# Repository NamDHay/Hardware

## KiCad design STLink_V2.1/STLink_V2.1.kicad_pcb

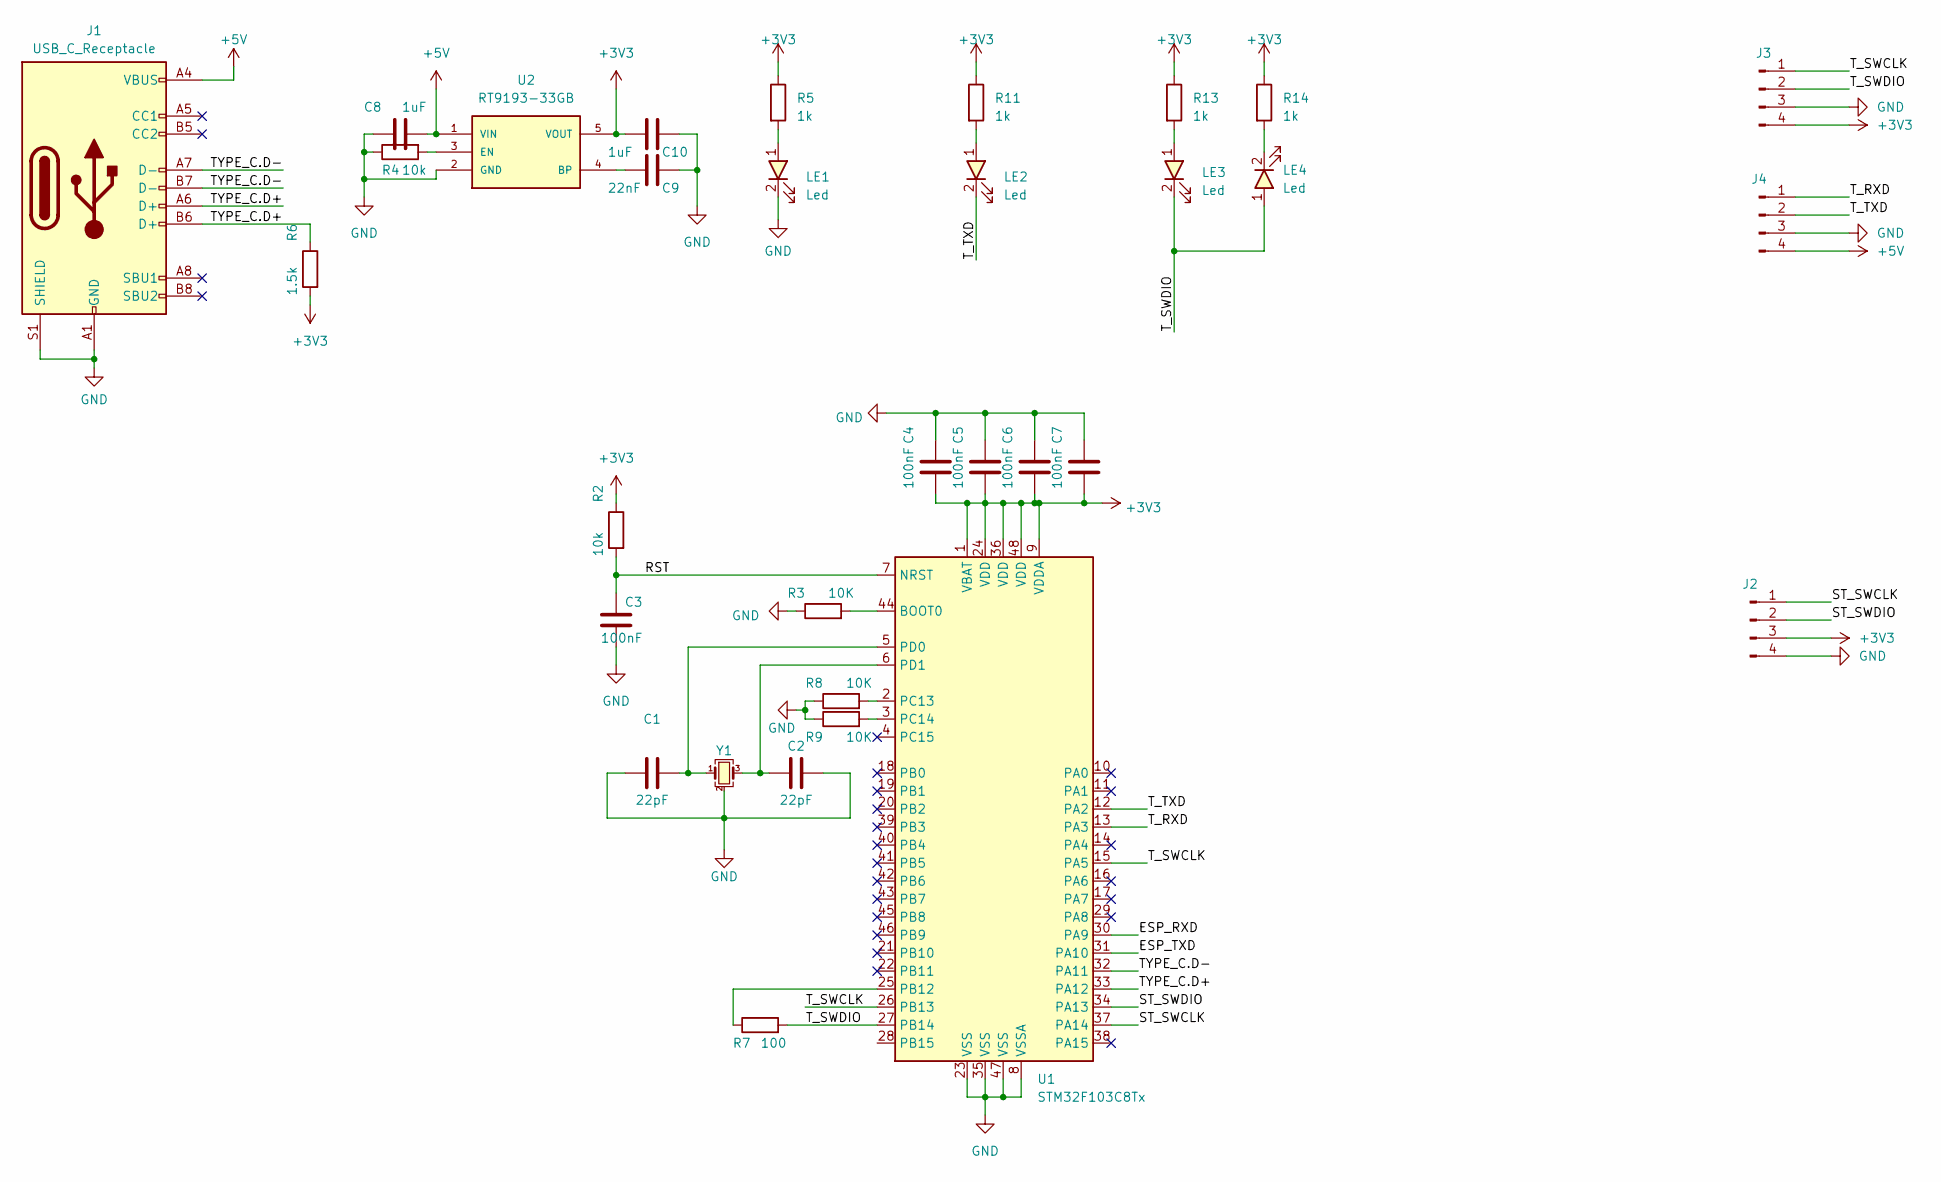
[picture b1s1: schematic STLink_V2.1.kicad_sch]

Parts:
C1, C2: 22pF; C_0603
C3, C4, C5, C6, C7: 100nF; C_0603
C8, C10: 1uF; C_0603
C9: 22nF; C_0603
J1: USB_C_Receptacle; USB_C_Receptacle_XKB_U262-16XN-4BVC11
J2, J3, J4: Conn_01x04_Pin; Conn-Horz-SMD-4P-2.54mm-PinHeader
LE1, LE2, LE3, LE4: Led; LED_0603
R2, R4: 10k; R_0603
R3, R8, R9: 10K; R_0603
R5, R11, R13, R14: 1k; R_0603
R6: 1.5k; R_0603
R7: 100; R_0603
U1: STM32F103C8Tx; LQFP-48_7x7mm_P0.5mm
U2: RT9193-33GB; SOT23-5
Y1: Crystal_GND24_Small; Crystal-SMD-4P-3.2x2.6mm-3225

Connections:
+3V3: C4.2, C5.2, C6.2, C7.2, C10.2, J2.3, J3.4, R2.1, R5.1, R6.2, R11.1, R13.1, R14.1, U1.1 (VBAT), U1.9 (VDDA), U1.24 (VDD), U1.36 (VDD), U1.48 (VDD), U2.5 (VOUT)
+5V: C8.2, J1.A4 (VBUS), J1.A9 (VBUS), J1.B4 (VBUS), J1.B9 (VBUS), J4.4, U2.1 (VIN)
/ESP_RXD: U1.30 (PA9)
/ESP_TXD: U1.31 (PA10)
/RST: C3.1, R2.2, U1.7 (NRST)
/ST_SWCLK: J2.1, U1.37 (PA14)
/ST_SWDIO: J2.2, U1.34 (PA13)
/TYPE_C.D+: J1.A6 (D+), J1.B6 (D+), R6.1, U1.33 (PA12)
/TYPE_C.D-: J1.A7 (D-), J1.B7 (D-), U1.32 (PA11)
/T_RXD: J4.1, U1.13 (PA3)
/T_SWCLK: J3.1, U1.15 (PA5), U1.26 (PB13)
/T_SWDIO: J3.2, LE3.2, LE4.1, R7.2, U1.27 (PB14)
/T_TXD: J4.2, LE2.2, U1.12 (PA2)
GND: C1.1, C2.2, C3.2, C4.1, C5.1, C6.1, C7.1, C8.1, C9.1, C10.1, J1.A1 (GND), J1.A12 (GND), J1.B1 (GND), J1.B12 (GND), J1.S1 (SHIELD), J2.4, J3.3, J4.3, LE1.2, R3.1, R4.1, R8.1, R9.1, U1.8 (VSSA), U1.23 (VSS), U1.35 (VSS), U1.47 (VSS), U2.2 (GND), Y1.2, Y1.4
unnamed: LE1.1, R5.2
unnamed: LE2.1, R11.2
unnamed: LE3.1, R13.2
unnamed: LE4.2, R14.2
unnamed: R3.2, U1.44 (BOOT0)
unnamed: R7.1, U1.25 (PB12)
unnamed: R8.2, U1.2 (PC13)
unnamed: R9.2, U1.3 (PC14)
unnamed: C1.2, U1.5 (PD0), Y1.1
unnamed: C2.1, U1.6 (PD1), Y1.3
unnamed: C9.2, U2.4 (BP)
unnamed: R4.2, U2.3 (EN)

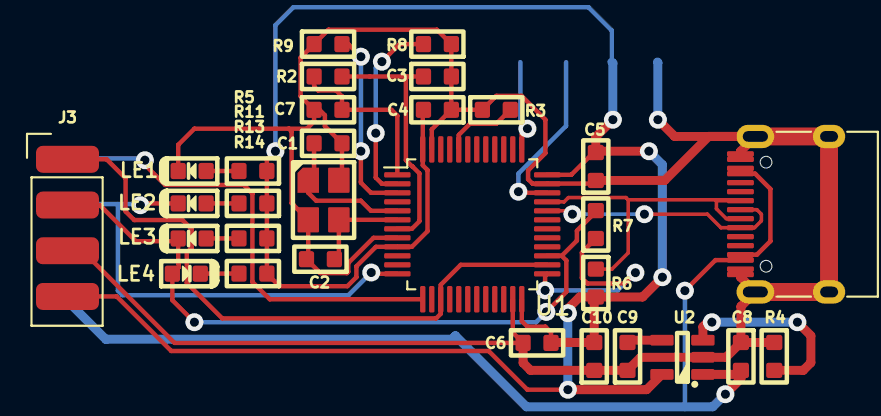
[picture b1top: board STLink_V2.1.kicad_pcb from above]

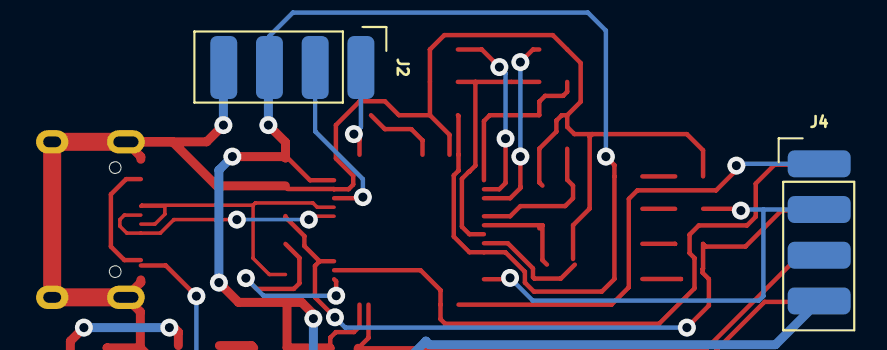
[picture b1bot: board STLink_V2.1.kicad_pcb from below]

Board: 2 copper layers, 32 parts (2 on the bottom side), 24 nets.

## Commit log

2024-01-06 HW685 module
2024-01-06 Complete HW-685 Schematic
2024-01-06 Complete HW685 Schematic
2024-02-15 Add STLink V2.1
2024-02-15 Complete Schematic
2024-02-19 complete pcb layout
